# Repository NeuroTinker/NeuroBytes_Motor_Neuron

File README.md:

# NeuroBytes Motor Neuron

The NeuroBytes Motor Neuron is an open-source hardware neuron simulator designed and sold by [NeuroTinker, LLC](http://www.neurotinker.com/). 

All NeuroBytes products are based on the ST32L0x series of ARM Cortex-M0+ 32-bit microcontrollers. The boards were designed in KiCad and Inkscape and are released under the terms of the Creative Commons Attribution-ShareAlike 4.0 license, available here: http://creativecommons.org/licenses/by-sa/4.0/. The NeuroBytes Motor Neuron is Certified Open Source Hardware as defined by [OSHWA](https://www.oshwa.org), certification number US000109.

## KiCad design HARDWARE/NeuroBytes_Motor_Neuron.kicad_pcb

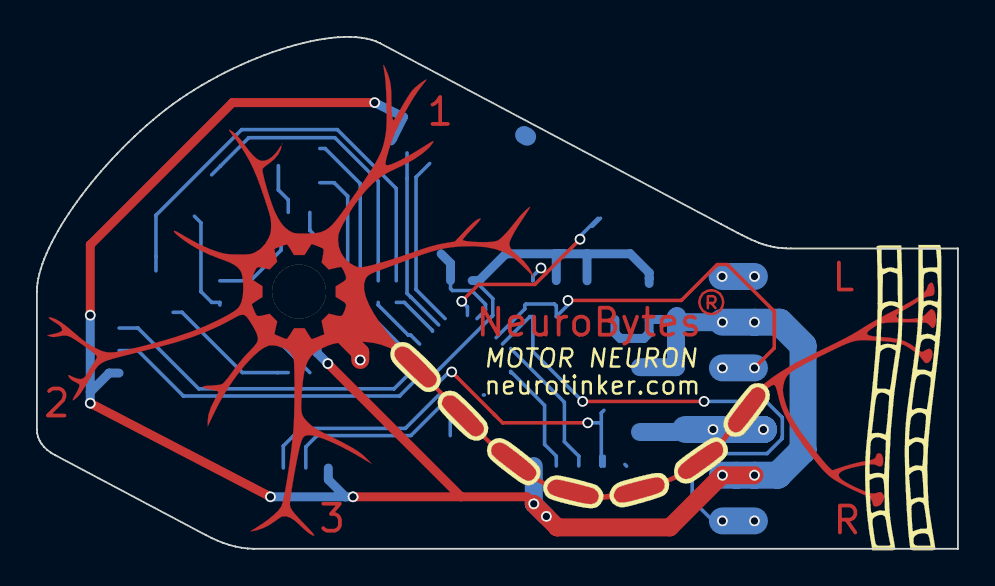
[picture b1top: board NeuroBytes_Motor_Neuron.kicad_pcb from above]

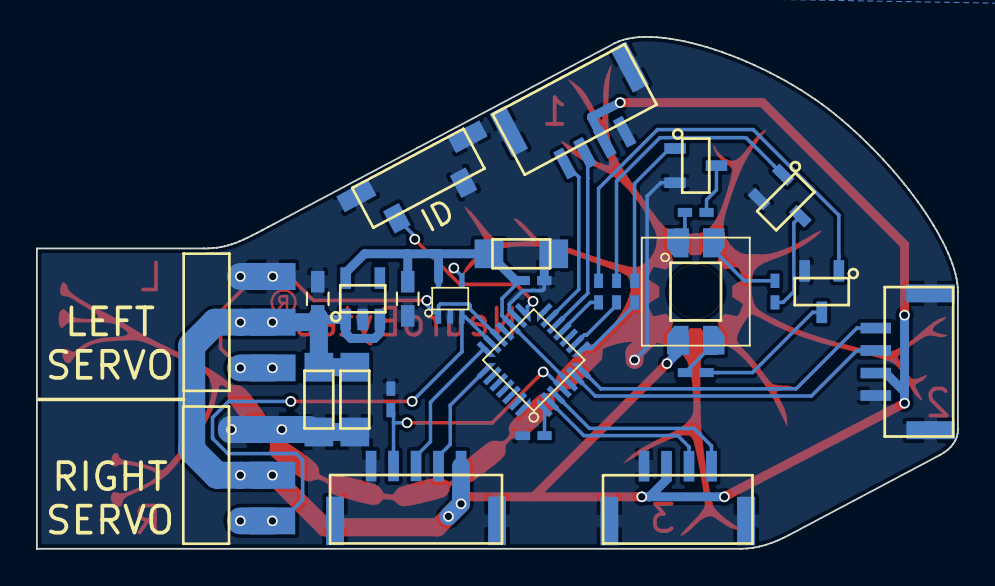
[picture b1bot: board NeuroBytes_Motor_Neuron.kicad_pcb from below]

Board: 2 copper layers, 51.2 x 28.4 mm, 28 parts (28 on the bottom side), 28 nets.

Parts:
C1, C4: 1u; C_0603_HandSoldering
C2: 10u; ZF_SMD_nonpol_1206
C3, C5: 0u1; ZF_SMD_NonPol_0402_cap
C6, C7: 22u; ZF_SMD_nonpol_1206
D1: LED_RABG; ZF_LED_RGB_SunLED_XZMDKCBDDG45S-9_cast
P1, P2, P3: JST_GH_4POS; ZF_CONN_JST_GH
P4, P5: SERVO_CONN; ZF_CONN_SERVO_HDR_SMT
P6: JST_GH_5-pos; ZF_CONN_JST_GH_5POS
Q1, Q2, Q3: MMBT3904; ZF_SOT23-3L
R1: 150; ZF_SMD_NonPol_0402
R2, R3: 100; ZF_SMD_NonPol_0402
R4: JMP; ZF_SMD_NonPol_0402
R5, R6, R7: 1k; ZF_SMD_NonPol_0402
SW1: SW_PUSH; ZF_SW_Momentary_SideMtg
U1: STM32L011Gx; ZF_IC_UFQFPN28-050
U2: LD3985G33R; ZF_SOT23-5L
U3: RClamp0503F; ZF_SMD_SOT-353

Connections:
+3V3: C2.1, C3.1, C4.1, U1.5, U1.17, U2.5, U3.5
+5V: C1.1, C6.1, C7.1, D1.2, P1.2, P2.2, P3.2, P4.2, P5.2, P6.5, U2.1, U2.3
D1EX: P1.4, U1.13
D1IN: P1.3, U1.12
D2EX: P2.4, U1.7
D2IN: P2.3, U1.6
D3EX: P3.4, U1.3
D3IN: P3.3, U1.2
GND: C1.2, C2.2, C3.2, C4.2, C5.2, C6.2, C7.2, P1.1, P2.1, P3.1, P4.1, P5.1, P6.1, Q1.2, Q2.2, Q3.2, R4.2, SW1.1, U1.16, U2.2, U3.2
IDENTIFY: SW1.2, U1.15, U3.4
LED_B: R6.2, U1.9
LED_G: R7.2, U1.11
LED_R: R5.2, U1.8
unnamed: D1.1, R1.1
unnamed: D1.3, R3.1
unnamed: D1.4, R2.1
unnamed: Q1.1, R5.1
unnamed: Q1.3, R1.2
unnamed: Q2.1, R6.1
unnamed: Q2.3, R2.2
unnamed: Q3.1, R7.1
unnamed: Q3.3, R3.2
unnamed: R4.1, U1.1
RESET: C5.1, P6.2, U1.4
SERVO_1: P4.3, U1.19, U3.1
SERVO_2: P5.3, U1.20, U3.3
SWCLK: P6.4, U1.22
SWDIO: P6.3, U1.21

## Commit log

2017-04-24 Added first gen hardware design files. No firmware yet beyond basic LED testing.
2017-05-15 First firmware commit
2017-05-15 servos work now
2017-05-15 changed PWM period to 20.3 Hz
2017-05-15 added schematic library submodule
2017-05-15 Hardware v3. Changed headers to 3-position JST GH headers. Modified graphics and PCB outline -- now convex-ish, and includes parallel faces for V-scoring and routing.
2017-05-26 Updated schematic global label 'SWITCH' to read 'IDENTIFY' (as with other NeuroBytes boards). Updated PCB LED footprint so silkscreen is correct (no routing changes).
2017-06-03 updated switch and header footprints. changed to nonpolarized tank caps. split resistor network and dual transistors into discrete components. other minor tweaks.
2017-08-11 added finerprint
2017-08-11 added elf
2017-08-11 modified gitignore
2017-08-11 allowed .elf
2017-08-11 add elf
2017-08-11 changed to 5-pin JST GH connector for power and programming. Added POWER label and increased ID label size to standard (1.2 / 0.17). Minor routing and labeling updates.
2017-08-11 device id
2017-08-11 changed fingerprint address
2017-08-11 new address
2017-08-11 fingerprint
2017-08-28 added kicad fonts to *.svg. added *.png render of pcb front.
2017-09-06 graphics updates
2017-09-06 illustration updates
2017-09-06 fresh *.png exports
2017-09-06 updated *.png image
2017-09-06 update readme.md with board front render
2017-09-07 updated schematic library
2017-09-07 removed old files
2017-09-14 testing protocol anti-aliasing
2017-09-14 fixed inhibitory/excitatory issue
2017-09-18 added mode switch to motor neuron for CR/std servos. changed lighting scheme (CR = cyan, std = yellow).
2017-09-19 updated servo labels
2017-09-20 updated graphics to reflect new servo markings
2017-09-22 updated board graphics to reflect updated gear. other minor updates.
2017-09-22 added .d and .map to .gitignore
2017-09-22 enforced new .gitignore
2017-09-22 removed old save file
2017-09-22 reloaded netlist. minor PCB changes.
2017-09-22 made elf
2017-10-03 minor page layout updates
2017-11-21 now using neurobytes common
2017-11-21 updated libopencm3
2017-11-21 fixed pin errors
2017-11-21 updated to new protocol
2017-11-21 cleaning up
2017-11-21 fixed version error
2017-11-27 adjusted PWM params and dendrite weightings
2017-11-28 support for PWM cmd
2017-11-29 fixed servo_zero
2017-11-29 define params for NID cmd
2017-11-29 added set dendrite weightings command
2017-11-29 command-less IDing
2017-11-29 updated license to CC-BY-SA 4.0. updated readme. added drawing no. to PCB.
2018-01-09 compatibility fixes
2018-02-01 fixed PWM params
2018-02-13 added ESD protection. minor routing changes. updated title block.
2018-03-08 minor PCB render updates
2018-03-08 added OSWHA logo to README.md
2018-03-15 increased blue servo range
2018-04-10 made elf.
2018-04-10 updated comms. made elf
2018-05-23 added fab files and BOM
2018-05-23 updated *.pos file
2018-05-31 added schematic *.pdf
2018-08-08 updated footprints to include B.Fab outlines. minor routing changes. re-generated Gerbers. added placement pdf.
2018-08-08 regen drill file
2018-12-29 write servo_type to eeprom
2018-12-29 cyan for CR mode

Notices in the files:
HARDWARE/NeuroBytes_Motor_Neuron.kicad_pcb:
(C) 2017 Zach Fredin
License: CC-BY-SA 4.0
